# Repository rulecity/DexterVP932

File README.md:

# Dexter - Philips 22VP932 Adapter
A simple adapter to enable Dexter to interface with games that used the Philips 22VP932 laserdisc player.  The only two games I know of are the Atari/European versions of Dragon's Lair and Space Ace.

# Background
When I was working on Dexter, a solid-state laserdisc player replacement for laserdisc arcade games, I wanted to add support for every laserdisc player on the main PCB.
However, it became apparent that I would probably never ship the product if I waited until every player was added to the main PCB.  So I designed the DB25 interface to be expandable and hopefully support future players down the road.
This VP932 adapter is the first adapter I made that extends from Dexter's DB25 interface.  Fortunately, it works correctly.

# PCBs
I created the PCB with Eagle v7.7.0.  I have briefly tested these files on Kicad v6 and they seem to work fine.

This was a smaller project so it was a little rushed.  You may notice that there is overlapping silkscreen on the PCB and the schematic page has no proper border.

# Bill of Materials
These are the actual spreadsheets I used when ordering parts for this PCB and assembling this PCB.

# Support
If you need help having PCBs made from the source files or with any other aspect of this repository, I offer commercial support: https://www.daphne-emu.com:9443/mediawiki/index.php/CommercialSupport

--Matt Ownby

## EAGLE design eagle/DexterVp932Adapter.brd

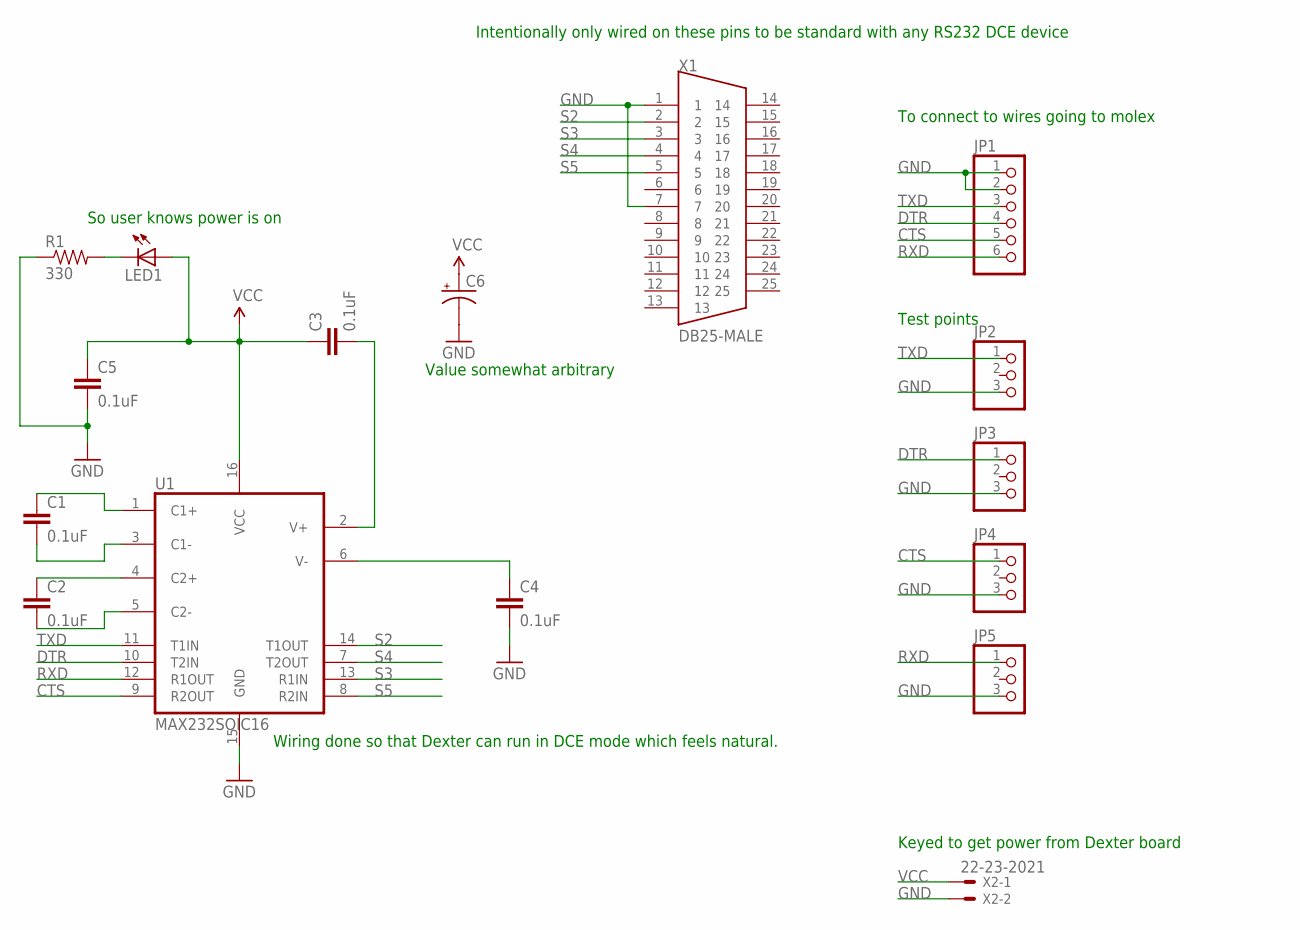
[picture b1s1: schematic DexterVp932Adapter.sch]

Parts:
C1, C2, C3, C4, C5: 0.1uF; 1206
C6: CAP_POLPTH2; CPOL-RADIAL-10UF-25V
JP1: PINHD-1X6; 1X06
JP2, JP3, JP4, JP5: PINHD-1X3; 1X03
LED1: LED1206; LED-1206
R1: 330; 1206
U1: MAX232SOIC16; SO016
X1: DB25-MALE
X2: 22-23-2021

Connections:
CTS: JP1.5, JP4.1, U1.9 (R2OUT)
DTR: JP1.4, JP3.1, U1.10 (T2IN)
FDFG: C2.2, U1.5 (C2-)
GND: C4.2, C5.2, C6.2 (-), JP1.1, JP1.2, JP2.3, JP3.3, JP4.3, JP5.3, R1.1, U1.15 (GND), X1.1, X1.7, X2.2
unnamed: C1.1, U1.1 (C1+)
unnamed: C1.2, U1.3 (C1-)
unnamed: C2.1, U1.4 (C2+)
unnamed: LED1.C, R1.2
unnamed: C4.1, U1.6 (V-)
unnamed: C3.2, U1.2 (V+)
RXD: JP1.6, JP5.1, U1.12 (R1OUT)
S2: U1.14 (T1OUT), X1.2
S3: U1.13 (R1IN), X1.3
S4: U1.7 (T2OUT), X1.4
S5: U1.8 (R2IN), X1.5
TXD: JP1.3, JP2.1, U1.11 (T1IN)
VCC: C3.1, C5.1, C6.1 (+), LED1.A, U1.16 (VCC), X2.1

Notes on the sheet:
Wiring done so that Dexter can run in DCE mode which feels natural.
Keyed to get power from Dexter board
Intentionally only wired on these pins to be standard with any RS232 DCE device
To connect to wires going to molex
Test points
So user knows power is on
Value somewhat arbitrary

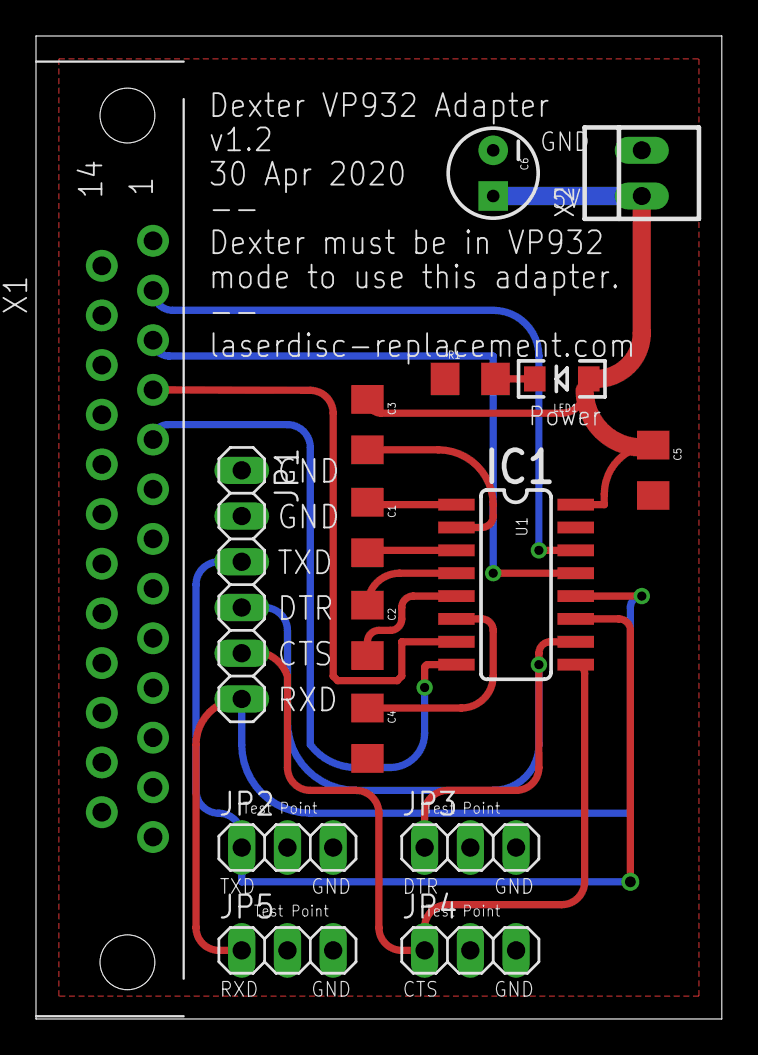
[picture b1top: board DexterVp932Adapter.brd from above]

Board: 2 copper layers, 38.1 x 54.6 mm, 16 parts (0 on the bottom side), 17 nets.

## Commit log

2024-09-18 adding Eagle PCB files and bill of materials
2024-09-18 added PDF versions of the billOfMaterials

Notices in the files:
parts and their libraries:
SparkFun: Licensing: CC v3.0 Share-Alike You are welcome to use this library for commercial purposes.
